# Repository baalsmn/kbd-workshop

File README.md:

# keyboard-workshop

Split-style ergonomic keyboards on a single PCB, designed in [Ergogen](https://ergogen.xyz)
4.2.1, finished in KiCad 10 and housed in 3D-printed cases. Developed with the help of
Anthropic's Claude Code.

*hachigo74, first build*

*kugo82, KiCad 3D render, no physical build yet*

## The Drive

Most open-source ergonomic keyboards are built around the English alphabet and keep
the key count low. Languages with a larger alphabet run out of keys quickly: Hungarian
alone needs nine accented vowels (á é í ó ö ő ú ü ű) on top of the Latin letters, and
these end up on layers or awkward key combinations.

This project aims for a keyboard with enough dedicated keys for such languages, while
keeping a split, angled, ergonomic layout. Each design is a mirrored two-half layout on
one PCB, with a Cirque trackpad and an OLED in the centre, an RP2040 controller (0xCB
Helios), low-profile Gateron KS-33 hot-swap switches and per-key RGB.

The layouts are designed primarily for Hungarian. The extra keys suit many other
languages too, for example Czech, Slovak, Polish, Turkish, Icelandic, the Nordic
languages or Japanese.

## Contents

| Folder | What |
|---|---|
| `kugo82/` | kugo82, 82 keys: hachigo74 plus an outer column and 1.25U modifiers |
| `hachigo74/` | hachigo74, 74 keys (kugo82 without the outer column); `kicad/` = its KiCad project |
| `tools/` | build, case (STL), STEP and render scripts; Fusion script; KiCad library / project scripts |
| `ergogen/` | Ergogen inputs: the design yamls (`kugo82`, `hachigo74`) and `footprints/` |
| `kicad-libraries/` | KiCad libraries: symbols (`keyboard-workshop`), footprints (`Keyboard`), and the 3D models (the one place they live: Ergogen builds and renders use them too) |
| `keyboard.kicad_dru` | DRC rules for every design |
| `datasheets/`, `drafts/` | part datasheets, sketches |

```bash
bash tools/build.sh kugo82     # Ergogen -> out/pcbs/kugo82.kicad_pcb + DRC
bash tools/case.sh kugo82      # -> kugo82/case/*.stl
bash tools/step.sh kugo82      # -> kugo82/case/step/*.step + case/fusion/kugo82_case.json
```

**Autodesk Fusion:** open the STEP files directly, or add `tools/fusion/KeyboardCase`
under Utilities → Scripts and Add-Ins and run it on a `case/fusion/*_case.json` to
get a parametric design (sketches + extrudes per part).

**KiCad project (hachigo74):** open `hachigo74/kicad/hachigo74.kicad_pro`. It is
portable (its own copy of the libraries in `libraries/`, every path
`${KIPRJMOD}`-relative), with the PCB and a schematic generated from it (ERC clean,
schematic parity clean). It is the master for routing from now on. The scripts that
made it, run with KiCad's Python after `tools/build.sh hachigo74`:

```bash
python tools/lib/kicad_footprints.py out/pcbs/hachigo74.kicad_pcb kicad-libraries --force   # footprints + 3D models
python tools/lib/kicad_symbols.py kicad-libraries                                           # symbol library (plain Python)
python tools/lib/kicad_project.py out/pcbs/hachigo74.kicad_pcb kicad-libraries hachigo74/kicad hachigo74   # project (--force to overwrite)
```

Needs: Node + `npm i -g ergogen@4.2.1`, KiCad 10, Python 3 (build123d installs itself
on first `step.sh`).

## Cost

First hachigo74 order (JLCPCB, 2026-10-23): 5 PCBs, 4 of them assembled by JLC (LEDs,
diodes, capacitors, resistor, FFC connector), delivered to Hungary by DHL Express with
duties paid: **EUR 221.84 in total**, about EUR 55 per assembled board. Not included:
the hand-soldered parts (hot-swap sockets, Helios, OLED), switches, keycaps, trackpad
and case. Breakdown: [ordering/README.md](ordering/README.md#orders).

All parts of one hachigo74 (PCB share, Helios, OLED, switches, sockets, stabilizers, trackpad, cable,
screws, filament): about EUR 131 (133 with the tilt wedge), without the shops' shipping, the wedge magnets and keycaps: [ordering/README.md](ordering/README.md#hachigo74-all-parts-of-one-keyboard-as-built-2026-11).

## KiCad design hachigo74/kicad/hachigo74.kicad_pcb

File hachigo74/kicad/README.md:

# hachigo74 KiCad project

Open `hachigo74.kicad_pro` in KiCad 10. The folder is self-contained and portable:
every symbol, footprint and 3D model path is `${KIPRJMOD}/libraries/...`.

| File | What |
|---|---|
| `hachigo74.kicad_pcb` | the Ergogen board (not routed yet), footprints linked to `Keyboard:<name>` and to their schematic symbols |
| `hachigo74.kicad_sch` | schematic generated from the board's netlist (net labels on every pin) |
| `hachigo74.kicad_dru` | custom DRC rule (0.2 mm LED pad-to-cutout, JLCPCB routed-edge minimum) |
| `libraries/` | project copy of `../../kicad libraries` (symbols `keyboard-workshop`, footprints `Keyboard`, 3D models) |
| `sym-lib-table`, `fp-lib-table` | project library tables |

Checked when generated: ERC 0 violations; DRC with schematic parity 0 issues (plus
the expected 2 silkscreen overlaps and 499 unrouted connections); the schematic
netlist matches the Ergogen board pad for pad (808 pads). Unused pins (GP0 = C1,
GP13-15, D+/D-, RST, the last LED's DOUT) carry no-connect flags.

This project is now the master for routing and schematic edits. Regenerating it
(`tools/lib/kicad_project.py ... --force`) overwrites the PCB and schematic.

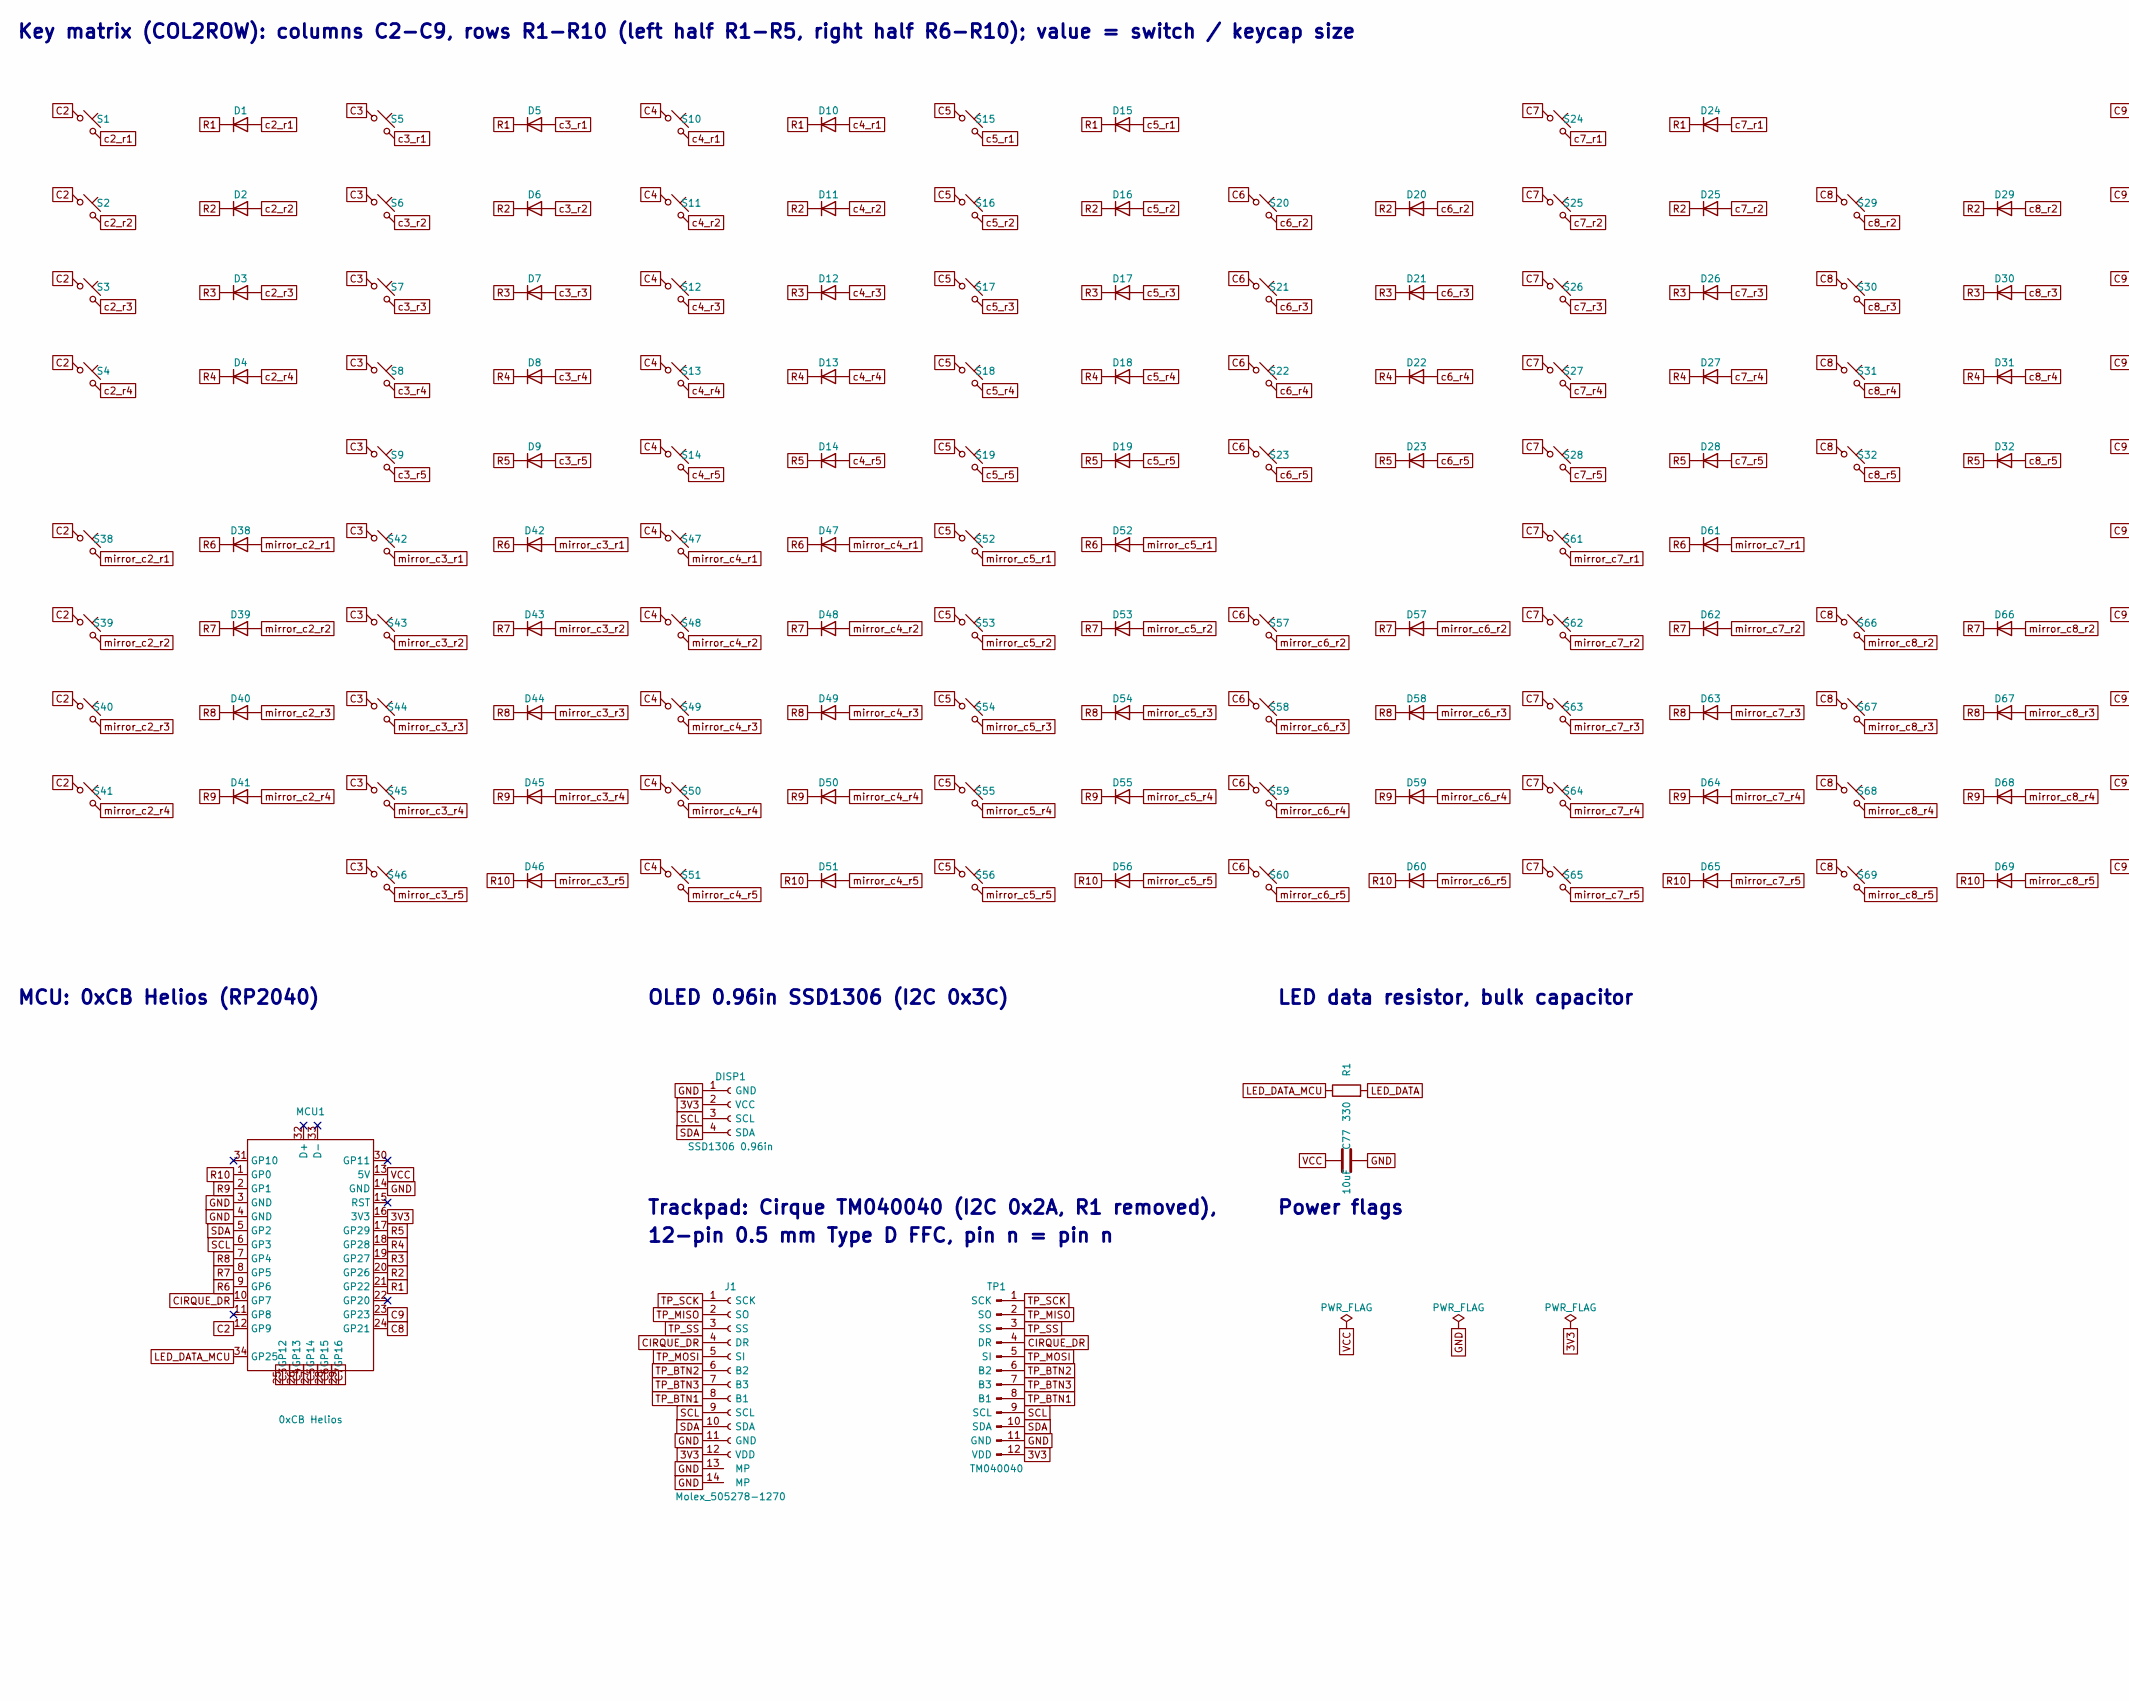
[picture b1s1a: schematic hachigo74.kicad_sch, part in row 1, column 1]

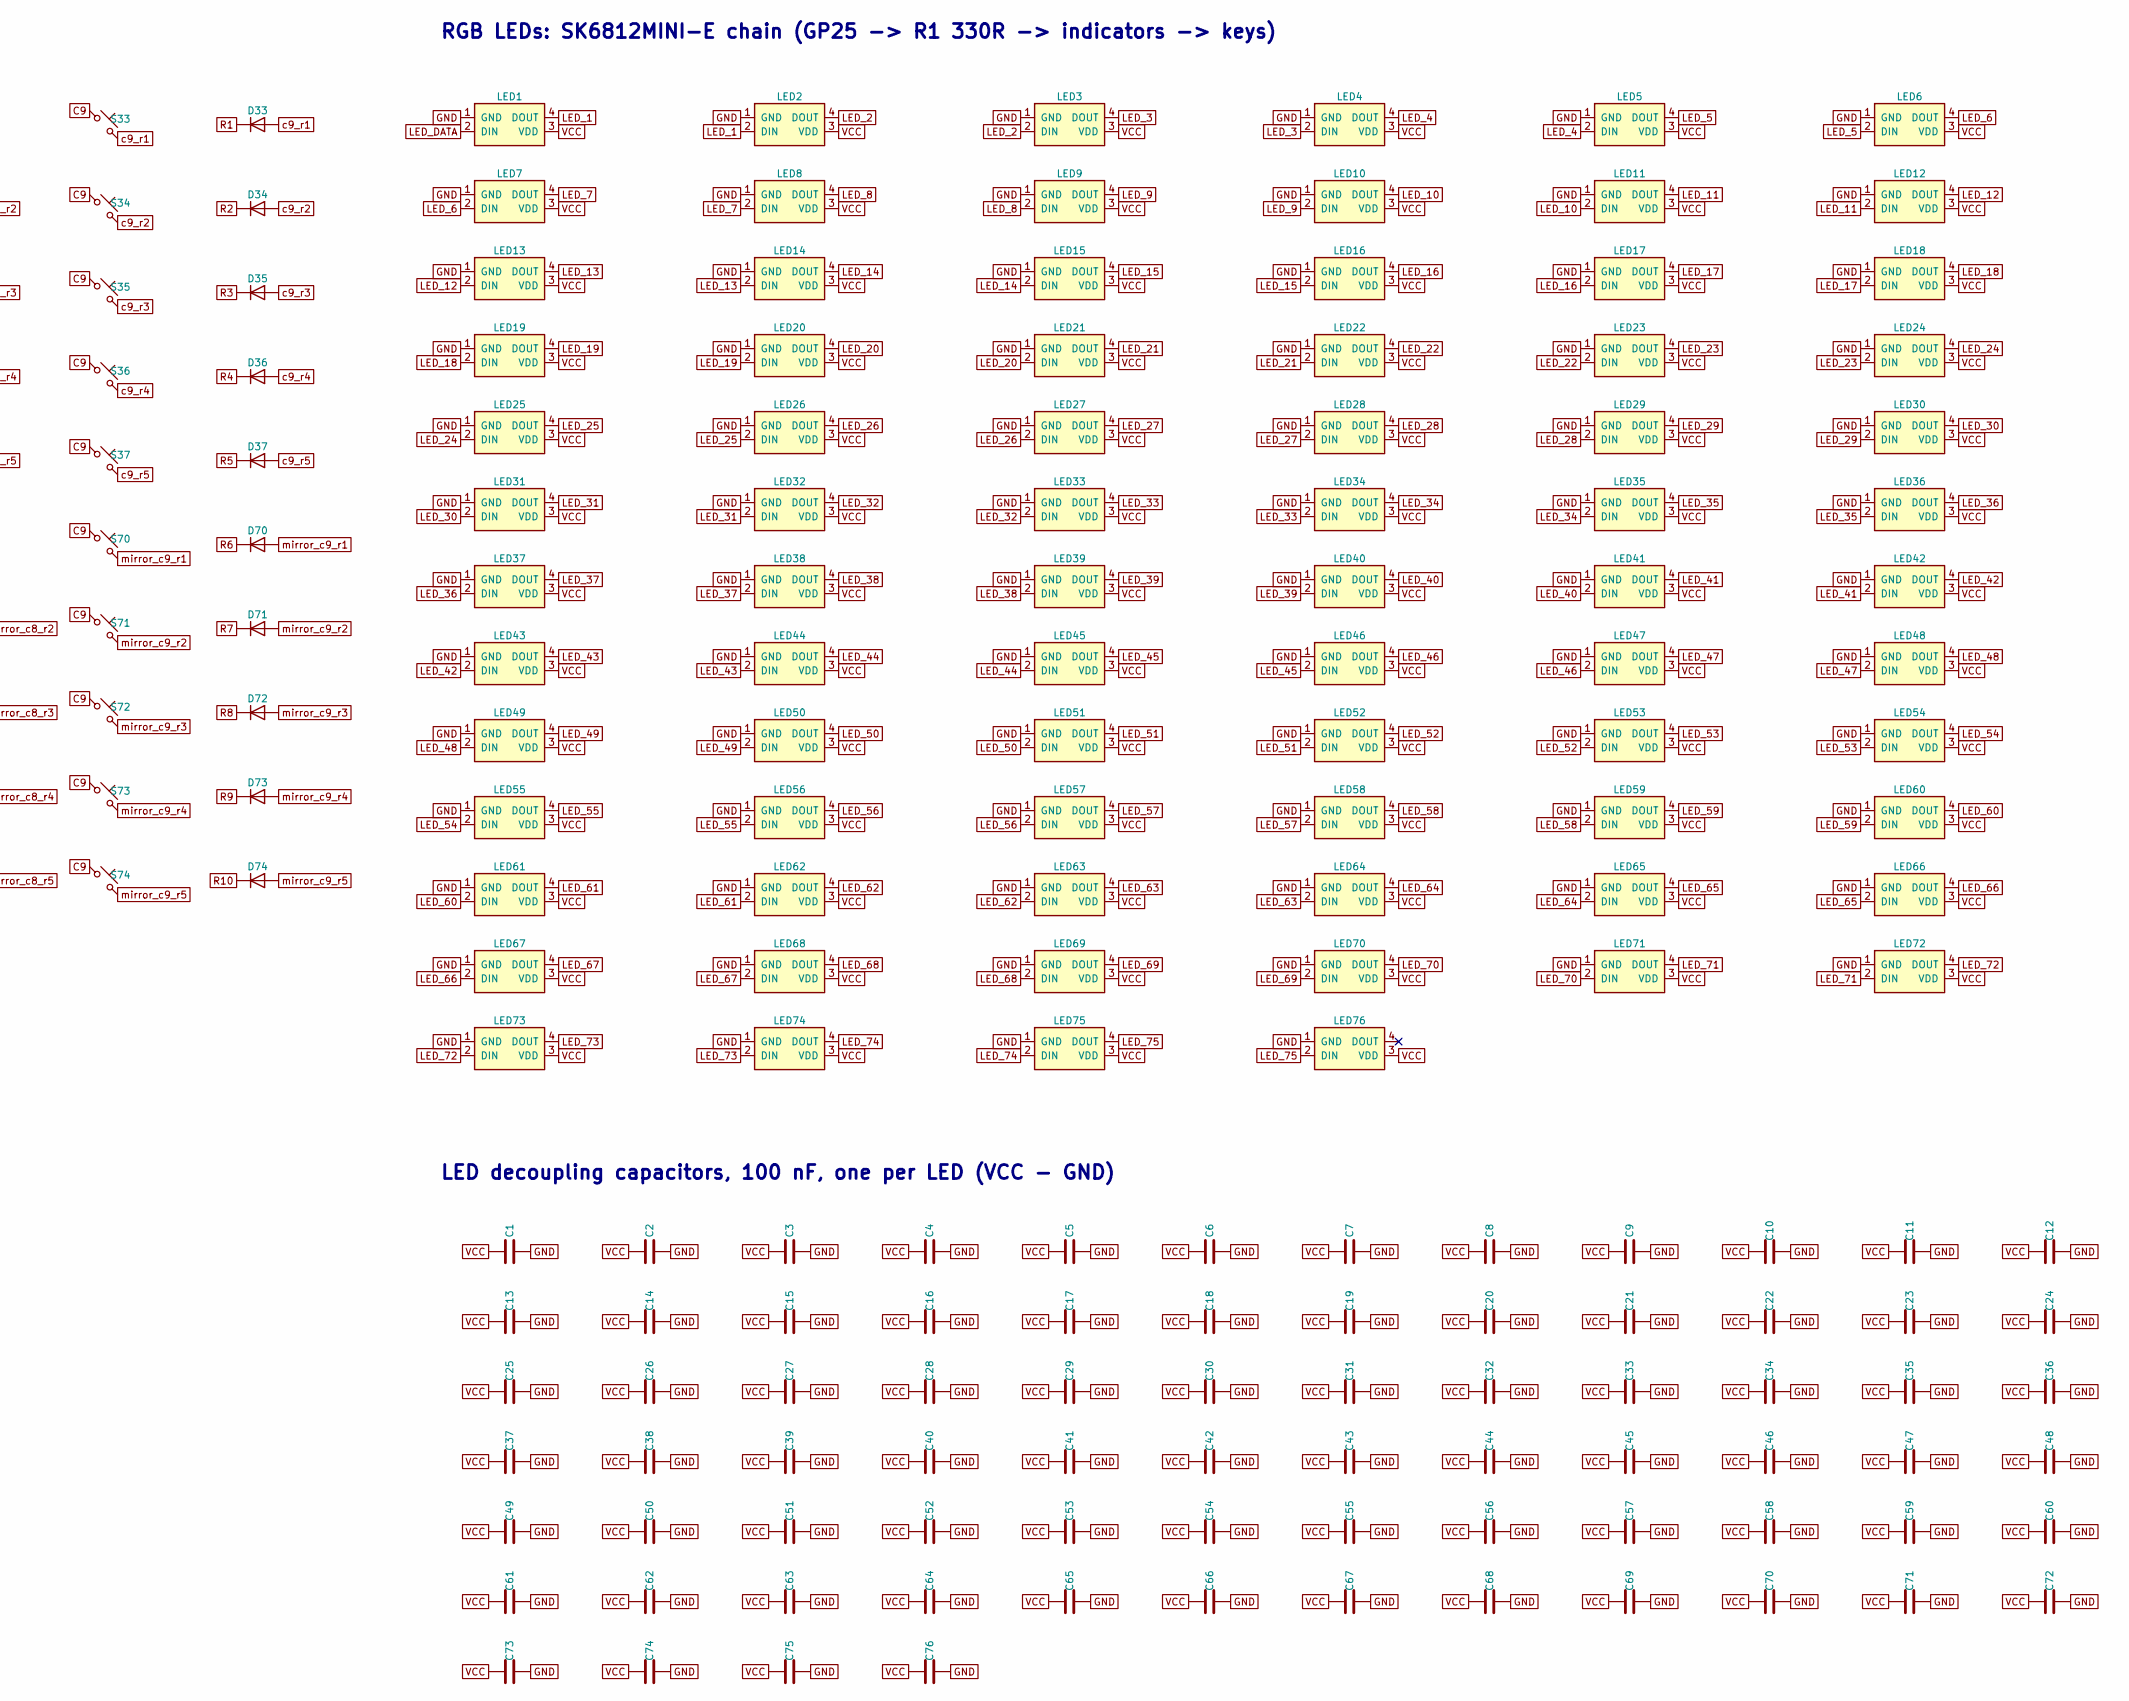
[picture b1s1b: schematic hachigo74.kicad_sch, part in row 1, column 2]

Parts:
C1, C2, C3, C4, C5, C6, C7, C8, C9, C10, C11, C12, C13, C14, C15, C16, C17, C18, C19, C20, C21, C22, C23, C24, C25, C26, C27, C28, C29, C30, C31, C32, C33, C34, C35, C36, C37, C38, C39, C40, C41, C42, C43, C44, C45, C46, C47, C48, C49, C50, C51, C52, C53, C54, C55, C56, C57, C58, C59, C60, C61, C62, C63, C64, C65, C66, C67, C68, C69, C70, C71, C72, C73, C74, C75, C76: 100nF; C_0603; LCSC C14663
C77: 10uF; C_0805; LCSC C15850
D1, D2, D3, D4, D5, D6, D7, D8, D9, D10, D11, D12, D13, D14, D15, D16, D17, D18, D19, D20, D21, D22, D23, D24, D25, D26, D27, D28, D29, D30, D31, D32, D33, D34, D35, D36, D37, D38, D39, D40, D41, D42, D43, D44, D45, D46, D47, D48, D49, D50, D51, D52, D53, D54, D55, D56, D57, D58, D59, D60, D61, D62, D63, D64, D65, D66, D67, D68, D69, D70, D71, D72, D73, D74: 1N4148W; D_SOD-123; LCSC C81598
DISP1: SSD1306 0.96in; OLED_0.96in_SSD1306_I2C
J1: Molex_505278-1270; Molex_505278-1270_12p; LCSC C47149418
LED1, LED2, LED3, LED4, LED5, LED6, LED7, LED8, LED9, LED10, LED11, LED12, LED13, LED14, LED15, LED16, LED17, LED18, LED19, LED20, LED21, LED22, LED23, LED24, LED25, LED26, LED27, LED28, LED29, LED30, LED31, LED32, LED33, LED34, LED35, LED36, LED37, LED38, LED39, LED40, LED41, LED42, LED43, LED44, LED45, LED46, LED47, LED48, LED49, LED50, LED51, LED52, LED53, LED54, LED55, LED56, LED57, LED58, LED59, LED60, LED61, LED62, LED63, LED64, LED65, LED66, LED67, LED68, LED69, LED70, LED71, LED72, LED73, LED74, LED75, LED76: SK6812MINI-E; LED_SK6812MINI-E_Reverse; LCSC C5149201
MCU1: 0xCB Helios; 0xCB_Helios
R1: 330; R_0603; LCSC C23138
S1, S2, S3, S4, S5, S6, S7, S8, S9, S10, S11, S12, S13, S14, S16, S17, S18, S19, S20, S21, S22, S23, S25, S26, S27, S28, S29, S30, S31, S32, S34, S35, S36, S37, S38, S39, S40, S41, S42, S43, S44, S45, S46, S47, S48, S49, S50, S51, S53, S54, S55, S56, S57, S58, S59, S60, S62, S63, S64, S65, S66, S67, S68, S69, S71, S72, S73, S74: KS-33 1U; Gateron_KS-33_Hotswap_1U; LCSC C18212911
S15, S52: KS-33 2U + KS-57; Gateron_KS-33_Hotswap_2U_Stab_KS-57; LCSC C18212911
S24, S33, S61, S70: KS-33 1.25U; Gateron_KS-33_Hotswap_1.25U; LCSC C18212911
TP1: TM040040

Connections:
3V3: DISP1.2 (VCC), J1.12 (VDD), MCU1.16 (3V3), TP1.12 (VDD)
C2: MCU1.12 (GP9), S1.1, S2.1, S3.1, S4.1, S38.1, S39.1, S40.1, S41.1
C3: MCU1.25 (GP12), S5.1, S6.1, S7.1, S8.1, S9.1, S42.1, S43.1, S44.1, S45.1, S46.1
C4: MCU1.26 (GP13), S10.1, S11.1, S12.1, S13.1, S14.1, S47.1, S48.1, S49.1, S50.1, S51.1
C5: MCU1.27 (GP14), S15.1, S16.1, S17.1, S18.1, S19.1, S52.1, S53.1, S54.1, S55.1, S56.1
C6: MCU1.28 (GP15), S20.1, S21.1, S22.1, S23.1, S57.1, S58.1, S59.1, S60.1
C7: MCU1.29 (GP16), S24.1, S25.1, S26.1, S27.1, S28.1, S61.1, S62.1, S63.1, S64.1, S65.1
C8: MCU1.24 (GP21), S29.1, S30.1, S31.1, S32.1, S66.1, S67.1, S68.1, S69.1
C9: MCU1.23 (GP23), S33.1, S34.1, S35.1, S36.1, S37.1, S70.1, S71.1, S72.1, S73.1, S74.1
CIRQUE_DR: J1.4 (DR), MCU1.10 (GP7), TP1.4 (DR)
GND: C1.2, C2.2, C3.2, C4.2, C5.2, C6.2, C7.2, C8.2, C9.2, C10.2, C11.2, C12.2, C13.2, C14.2, C15.2, C16.2, C17.2, C18.2, C19.2, C20.2, C21.2, C22.2, C23.2, C24.2, C25.2, C26.2, C27.2, C28.2, C29.2, C30.2, C31.2, C32.2, C33.2, C34.2, C35.2, C36.2, C37.2, C38.2, C39.2, C40.2, C41.2, C42.2, C43.2, C44.2, C45.2, C46.2, C47.2, C48.2, C49.2, C50.2, C51.2, C52.2, C53.2, C54.2, C55.2, C56.2, C57.2, C58.2, C59.2, C60.2, C61.2, C62.2, C63.2, C64.2, C65.2, C66.2, C67.2, C68.2, C69.2, C70.2, C71.2, C72.2, C73.2, C74.2, C75.2, C76.2, C77.2, DISP1.1 (GND), J1.11 (GND), J1.13 (MP), J1.14 (MP), LED1.1 (GND), LED2.1 (GND), LED3.1 (GND), LED4.1 (GND), LED5.1 (GND), LED6.1 (GND), LED7.1 (GND), LED8.1 (GND), LED9.1 (GND), LED10.1 (GND), LED11.1 (GND), LED12.1 (GND), LED13.1 (GND), LED14.1 (GND), LED15.1 (GND), LED16.1 (GND), LED17.1 (GND), LED18.1 (GND), LED19.1 (GND), LED20.1 (GND), LED21.1 (GND), LED22.1 (GND), LED23.1 (GND), LED24.1 (GND), LED25.1 (GND), LED26.1 (GND), LED27.1 (GND), LED28.1 (GND), LED29.1 (GND), LED30.1 (GND), LED31.1 (GND), LED32.1 (GND), LED33.1 (GND), LED34.1 (GND), LED35.1 (GND), LED36.1 (GND), LED37.1 (GND), LED38.1 (GND), LED39.1 (GND), LED40.1 (GND), LED41.1 (GND), LED42.1 (GND), LED43.1 (GND), LED44.1 (GND), LED45.1 (GND), LED46.1 (GND), LED47.1 (GND), LED48.1 (GND), LED49.1 (GND), LED50.1 (GND), LED51.1 (GND), LED52.1 (GND), LED53.1 (GND), LED54.1 (GND), LED55.1 (GND), LED56.1 (GND), LED57.1 (GND), LED58.1 (GND), LED59.1 (GND), LED60.1 (GND), LED61.1 (GND), LED62.1 (GND), LED63.1 (GND), LED64.1 (GND), LED65.1 (GND), LED66.1 (GND), LED67.1 (GND), LED68.1 (GND), LED69.1 (GND), LED70.1 (GND), LED71.1 (GND), LED72.1 (GND), LED73.1 (GND), LED74.1 (GND), LED75.1 (GND), LED76.1 (GND), MCU1.3 (GND), MCU1.4 (GND), MCU1.14 (GND), TP1.11 (GND)
LED_1: LED1.4 (DOUT), LED2.2 (DIN)
LED_2: LED2.4 (DOUT), LED3.2 (DIN)
LED_3: LED3.4 (DOUT), LED4.2 (DIN)
LED_4: LED4.4 (DOUT), LED5.2 (DIN)
LED_5: LED5.4 (DOUT), LED6.2 (DIN)
LED_6: LED6.4 (DOUT), LED7.2 (DIN)
LED_7: LED7.4 (DOUT), LED8.2 (DIN)
LED_8: LED8.4 (DOUT), LED9.2 (DIN)
LED_9: LED9.4 (DOUT), LED10.2 (DIN)
LED_10: LED10.4 (DOUT), LED11.2 (DIN)
LED_11: LED11.4 (DOUT), LED12.2 (DIN)
LED_12: LED12.4 (DOUT), LED13.2 (DIN)
LED_13: LED13.4 (DOUT), LED14.2 (DIN)
LED_14: LED14.4 (DOUT), LED15.2 (DIN)
LED_15: LED15.4 (DOUT), LED16.2 (DIN)
LED_16: LED16.4 (DOUT), LED17.2 (DIN)
LED_17: LED17.4 (DOUT), LED18.2 (DIN)
LED_18: LED18.4 (DOUT), LED19.2 (DIN)
LED_19: LED19.4 (DOUT), LED20.2 (DIN)
LED_20: LED20.4 (DOUT), LED21.2 (DIN)
LED_21: LED21.4 (DOUT), LED22.2 (DIN)
LED_22: LED22.4 (DOUT), LED23.2 (DIN)
LED_23: LED23.4 (DOUT), LED24.2 (DIN)
LED_24: LED24.4 (DOUT), LED25.2 (DIN)
LED_25: LED25.4 (DOUT), LED26.2 (DIN)
LED_26: LED26.4 (DOUT), LED27.2 (DIN)
LED_27: LED27.4 (DOUT), LED28.2 (DIN)
LED_28: LED28.4 (DOUT), LED29.2 (DIN)
LED_29: LED29.4 (DOUT), LED30.2 (DIN)
LED_30: LED30.4 (DOUT), LED31.2 (DIN)
LED_31: LED31.4 (DOUT), LED32.2 (DIN)
LED_32: LED32.4 (DOUT), LED33.2 (DIN)
LED_33: LED33.4 (DOUT), LED34.2 (DIN)
LED_34: LED34.4 (DOUT), LED35.2 (DIN)
LED_35: LED35.4 (DOUT), LED36.2 (DIN)
LED_36: LED36.4 (DOUT), LED37.2 (DIN)
LED_37: LED37.4 (DOUT), LED38.2 (DIN)
LED_38: LED38.4 (DOUT), LED39.2 (DIN)
LED_39: LED39.4 (DOUT), LED40.2 (DIN)
LED_40: LED40.4 (DOUT), LED41.2 (DIN)
LED_41: LED41.4 (DOUT), LED42.2 (DIN)
LED_42: LED42.4 (DOUT), LED43.2 (DIN)
LED_43: LED43.4 (DOUT), LED44.2 (DIN)
LED_44: LED44.4 (DOUT), LED45.2 (DIN)
LED_45: LED45.4 (DOUT), LED46.2 (DIN)
LED_46: LED46.4 (DOUT), LED47.2 (DIN)
LED_47: LED47.4 (DOUT), LED48.2 (DIN)
LED_48: LED48.4 (DOUT), LED49.2 (DIN)
LED_49: LED49.4 (DOUT), LED50.2 (DIN)
LED_50: LED50.4 (DOUT), LED51.2 (DIN)
LED_51: LED51.4 (DOUT), LED52.2 (DIN)
LED_52: LED52.4 (DOUT), LED53.2 (DIN)
LED_53: LED53.4 (DOUT), LED54.2 (DIN)
LED_54: LED54.4 (DOUT), LED55.2 (DIN)
LED_55: LED55.4 (DOUT), LED56.2 (DIN)
LED_56: LED56.4 (DOUT), LED57.2 (DIN)
LED_57: LED57.4 (DOUT), LED58.2 (DIN)
LED_58: LED58.4 (DOUT), LED59.2 (DIN)
LED_59: LED59.4 (DOUT), LED60.2 (DIN)
LED_60: LED60.4 (DOUT), LED61.2 (DIN)
LED_61: LED61.4 (DOUT), LED62.2 (DIN)
LED_62: LED62.4 (DOUT), LED63.2 (DIN)
LED_63: LED63.4 (DOUT), LED64.2 (DIN)
LED_64: LED64.4 (DOUT), LED65.2 (DIN)
LED_65: LED65.4 (DOUT), LED66.2 (DIN)
LED_66: LED66.4 (DOUT), LED67.2 (DIN)
LED_67: LED67.4 (DOUT), LED68.2 (DIN)
LED_68: LED68.4 (DOUT), LED69.2 (DIN)
LED_69: LED69.4 (DOUT), LED70.2 (DIN)
LED_70: LED70.4 (DOUT), LED71.2 (DIN)
LED_71: LED71.4 (DOUT), LED72.2 (DIN)
LED_72: LED72.4 (DOUT), LED73.2 (DIN)
LED_73: LED73.4 (DOUT), LED74.2 (DIN)
LED_74: LED74.4 (DOUT), LED75.2 (DIN)
LED_75: LED75.4 (DOUT), LED76.2 (DIN)
LED_DATA: LED1.2 (DIN), R1.2
LED_DATA_MCU: MCU1.34 (GP25), R1.1
R1: D1.1 (K), D5.1 (K), D10.1 (K), D15.1 (K), D24.1 (K), D33.1 (K), MCU1.21 (GP22)
R2: D2.1 (K), D6.1 (K), D11.1 (K), D16.1 (K), D20.1 (K), D25.1 (K), D29.1 (K), D34.1 (K), MCU1.20 (GP26)
R3: D3.1 (K), D7.1 (K), D12.1 (K), D17.1 (K), D21.1 (K), D26.1 (K), D30.1 (K), D35.1 (K), MCU1.19 (GP27)
R4: D4.1 (K), D8.1 (K), D13.1 (K), D18.1 (K), D22.1 (K), D27.1 (K), D31.1 (K), D36.1 (K), MCU1.18 (GP28)
R5: D9.1 (K), D14.1 (K), D19.1 (K), D23.1 (K), D28.1 (K), D32.1 (K), D37.1 (K), MCU1.17 (GP29)
R6: D38.1 (K), D42.1 (K), D47.1 (K), D52.1 (K), D61.1 (K), D70.1 (K), MCU1.9 (GP6)
R7: D39.1 (K), D43.1 (K), D48.1 (K), D53.1 (K), D57.1 (K), D62.1 (K), D66.1 (K), D71.1 (K), MCU1.8 (GP5)
R8: D40.1 (K), D44.1 (K), D49.1 (K), D54.1 (K), D58.1 (K), D63.1 (K), D67.1 (K), D72.1 (K), MCU1.7 (GP4)
R9: D41.1 (K), D45.1 (K), D50.1 (K), D55.1 (K), D59.1 (K), D64.1 (K), D68.1 (K), D73.1 (K), MCU1.2 (GP1)
R10: D46.1 (K), D51.1 (K), D56.1 (K), D60.1 (K), D65.1 (K), D69.1 (K), D74.1 (K), MCU1.1 (GP0)
SCL: DISP1.3 (SCL), J1.9 (SCL), MCU1.6 (GP3), TP1.9 (SCL)
SDA: DISP1.4 (SDA), J1.10 (SDA), MCU1.5 (GP2), TP1.10 (SDA)
TP_BTN1: J1.8 (B1), TP1.8 (B1)
TP_BTN2: J1.6 (B2), TP1.6 (B2)
TP_BTN3: J1.7 (B3), TP1.7 (B3)
TP_MISO: J1.2 (SO), TP1.2 (SO)
TP_MOSI: J1.5 (SI), TP1.5 (SI)
TP_SCK: J1.1 (SCK), TP1.1 (SCK)
TP_SS: J1.3 (SS), TP1.3 (SS)
VCC: C1.1, C2.1, C3.1, C4.1, C5.1, C6.1, C7.1, C8.1, C9.1, C10.1, C11.1, C12.1, C13.1, C14.1, C15.1, C16.1, C17.1, C18.1, C19.1, C20.1, C21.1, C22.1, C23.1, C24.1, C25.1, C26.1, C27.1, C28.1, C29.1, C30.1, C31.1, C32.1, C33.1, C34.1, C35.1, C36.1, C37.1, C38.1, C39.1, C40.1, C41.1, C42.1, C43.1, C44.1, C45.1, C46.1, C47.1, C48.1, C49.1, C50.1, C51.1, C52.1, C53.1, C54.1, C55.1, C56.1, C57.1, C58.1, C59.1, C60.1, C61.1, C62.1, C63.1, C64.1, C65.1, C66.1, C67.1, C68.1, C69.1, C70.1, C71.1, C72.1, C73.1, C74.1, C75.1, C76.1, C77.1, LED1.3 (VDD), LED2.3 (VDD), LED3.3 (VDD), LED4.3 (VDD), LED5.3 (VDD), LED6.3 (VDD), LED7.3 (VDD), LED8.3 (VDD), LED9.3 (VDD), LED10.3 (VDD), LED11.3 (VDD), LED12.3 (VDD), LED13.3 (VDD), LED14.3 (VDD), LED15.3 (VDD), LED16.3 (VDD), LED17.3 (VDD), LED18.3 (VDD), LED19.3 (VDD), LED20.3 (VDD), LED21.3 (VDD), LED22.3 (VDD), LED23.3 (VDD), LED24.3 (VDD), LED25.3 (VDD), LED26.3 (VDD), LED27.3 (VDD), LED28.3 (VDD), LED29.3 (VDD), LED30.3 (VDD), LED31.3 (VDD), LED32.3 (VDD), LED33.3 (VDD), LED34.3 (VDD), LED35.3 (VDD), LED36.3 (VDD), LED37.3 (VDD), LED38.3 (VDD), LED39.3 (VDD), LED40.3 (VDD), LED41.3 (VDD), LED42.3 (VDD), LED43.3 (VDD), LED44.3 (VDD), LED45.3 (VDD), LED46.3 (VDD), LED47.3 (VDD), LED48.3 (VDD), LED49.3 (VDD), LED50.3 (VDD), LED51.3 (VDD), LED52.3 (VDD), LED53.3 (VDD), LED54.3 (VDD), LED55.3 (VDD), LED56.3 (VDD), LED57.3 (VDD), LED58.3 (VDD), LED59.3 (VDD), LED60.3 (VDD), LED61.3 (VDD), LED62.3 (VDD), LED63.3 (VDD), LED64.3 (VDD), LED65.3 (VDD), LED66.3 (VDD), LED67.3 (VDD), LED68.3 (VDD), LED69.3 (VDD), LED70.3 (VDD), LED71.3 (VDD), LED72.3 (VDD), LED73.3 (VDD), LED74.3 (VDD), LED75.3 (VDD), LED76.3 (VDD), MCU1.13 (5V)
c2_r1: D1.2 (A), S1.2
c2_r2: D2.2 (A), S2.2
c2_r3: D3.2 (A), S3.2
c2_r4: D4.2 (A), S4.2
c3_r1: D5.2 (A), S5.2
c3_r2: D6.2 (A), S6.2
c3_r3: D7.2 (A), S7.2
c3_r4: D8.2 (A), S8.2
c3_r5: D9.2 (A), S9.2
c4_r1: D10.2 (A), S10.2
c4_r2: D11.2 (A), S11.2
c4_r3: D12.2 (A), S12.2
c4_r4: D13.2 (A), S13.2
c4_r5: D14.2 (A), S14.2
c5_r1: D15.2 (A), S15.2
c5_r2: D16.2 (A), S16.2
c5_r3: D17.2 (A), S17.2
c5_r4: D18.2 (A), S18.2
c5_r5: D19.2 (A), S19.2
c6_r2: D20.2 (A), S20.2
c6_r3: D21.2 (A), S21.2
c6_r4: D22.2 (A), S22.2
c6_r5: D23.2 (A), S23.2
c7_r1: D24.2 (A), S24.2
c7_r2: D25.2 (A), S25.2
c7_r3: D26.2 (A), S26.2
c7_r4: D27.2 (A), S27.2
c7_r5: D28.2 (A), S28.2
c8_r2: D29.2 (A), S29.2
c8_r3: D30.2 (A), S30.2
c8_r4: D31.2 (A), S31.2
c8_r5: D32.2 (A), S32.2
c9_r1: D33.2 (A), S33.2
c9_r2: D34.2 (A), S34.2
c9_r3: D35.2 (A), S35.2
c9_r4: D36.2 (A), S36.2
c9_r5: D37.2 (A), S37.2
mirror_c2_r1: D38.2 (A), S38.2
mirror_c2_r2: D39.2 (A), S39.2
mirror_c2_r3: D40.2 (A), S40.2
mirror_c2_r4: D41.2 (A), S41.2
mirror_c3_r1: D42.2 (A), S42.2
mirror_c3_r2: D43.2 (A), S43.2
mirror_c3_r3: D44.2 (A), S44.2
mirror_c3_r4: D45.2 (A), S45.2
mirror_c3_r5: D46.2 (A), S46.2
mirror_c4_r1: D47.2 (A), S47.2
mirror_c4_r2: D48.2 (A), S48.2
mirror_c4_r3: D49.2 (A), S49.2
mirror_c4_r4: D50.2 (A), S50.2
mirror_c4_r5: D51.2 (A), S51.2
mirror_c5_r1: D52.2 (A), S52.2
mirror_c5_r2: D53.2 (A), S53.2
mirror_c5_r3: D54.2 (A), S54.2
mirror_c5_r4: D55.2 (A), S55.2
mirror_c5_r5: D56.2 (A), S56.2
mirror_c6_r2: D57.2 (A), S57.2
mirror_c6_r3: D58.2 (A), S58.2
mirror_c6_r4: D59.2 (A), S59.2
mirror_c6_r5: D60.2 (A), S60.2
mirror_c7_r1: D61.2 (A), S61.2
mirror_c7_r2: D62.2 (A), S62.2
mirror_c7_r3: D63.2 (A), S63.2
mirror_c7_r4: D64.2 (A), S64.2
mirror_c7_r5: D65.2 (A), S65.2
mirror_c8_r2: D66.2 (A), S66.2
mirror_c8_r3: D67.2 (A), S67.2
mirror_c8_r4: D68.2 (A), S68.2
mirror_c8_r5: D69.2 (A), S69.2
mirror_c9_r1: D70.2 (A), S70.2
mirror_c9_r2: D71.2 (A), S71.2
mirror_c9_r3: D72.2 (A), S72.2
mirror_c9_r4: D73.2 (A), S73.2
mirror_c9_r5: D74.2 (A), S74.2

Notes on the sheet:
Trackpad: Cirque TM040040 (I2C 0x2A, R1 removed),
RGB LEDs: SK6812MINI-E chain (GP25 -> R1 330R -> indicators -> keys)
LED data resistor, bulk capacitor
OLED 0.96in SSD1306 (I2C 0x3C)
Key matrix (COL2ROW): columns C2-C9, rows R1-R10 (left half R1-R5, right half R6-R10); value = switch / keycap size
LED decoupling capacitors, 100 nF, one per LED (VCC - GND)
Power flags
MCU: 0xCB Helios (RP2040)
12-pin 0.5 mm Type D FFC, pin n = pin n

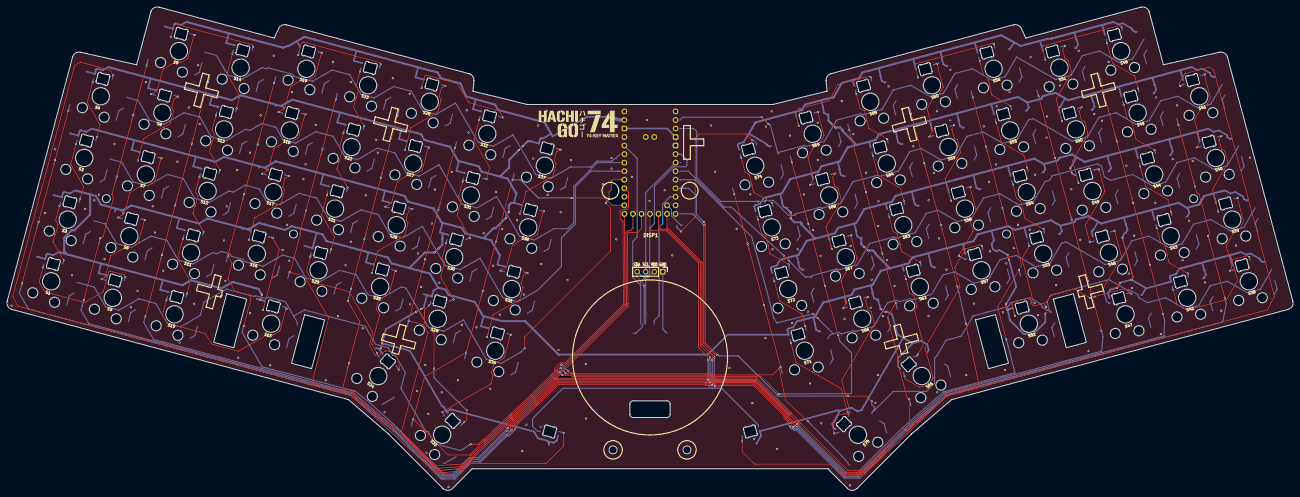
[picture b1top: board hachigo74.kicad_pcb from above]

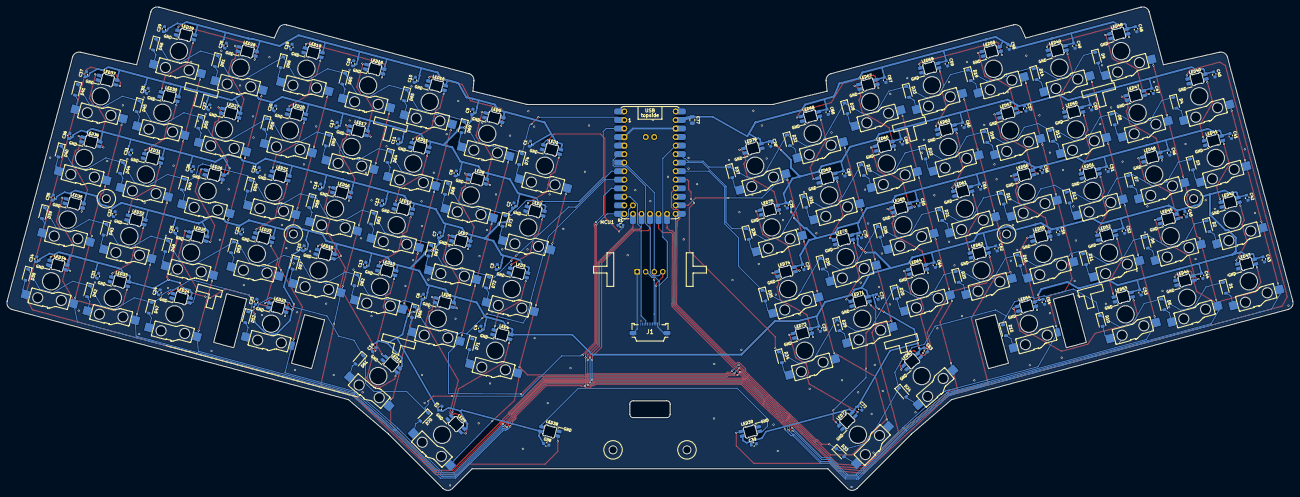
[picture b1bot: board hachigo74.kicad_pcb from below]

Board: 2 copper layers, 382.7 x 143.8 mm, 307 parts (304 on the bottom side), 175 nets.

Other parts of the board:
LOGO1: Logo_hachigo74
MECH1: Cirque_TM040040_3D
